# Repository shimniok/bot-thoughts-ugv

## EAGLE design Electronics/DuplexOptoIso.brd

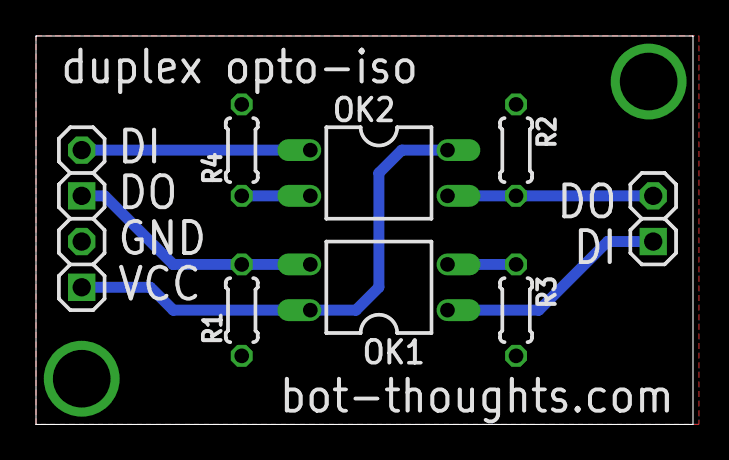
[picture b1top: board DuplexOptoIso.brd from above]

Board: 2 copper layers, 36.5 x 21.6 mm, 9 parts (0 on the bottom side), 8 nets.

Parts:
JP1: 1IN2OUT; 1X02-S
JP2: 1OUT2IN; 1X02-S
JP3: POWER; 1X02-S
OK1, OK2: PC817; DIL04
R1, R2, R3, R4: 0204/5

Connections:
5V: JP3.1, OK1.4, OK2.4
GND: JP3.2, R1.1, R2.1, R3.1, R4.1
IN1: JP1.1, OK1.1
IN2: JP2.2, OK2.1
unnamed: OK1.2, R3.2
unnamed: OK2.2, R4.2
OUT1: JP2.1, OK1.3, R1.2
OUT2: JP1.2, OK2.3, R2.2

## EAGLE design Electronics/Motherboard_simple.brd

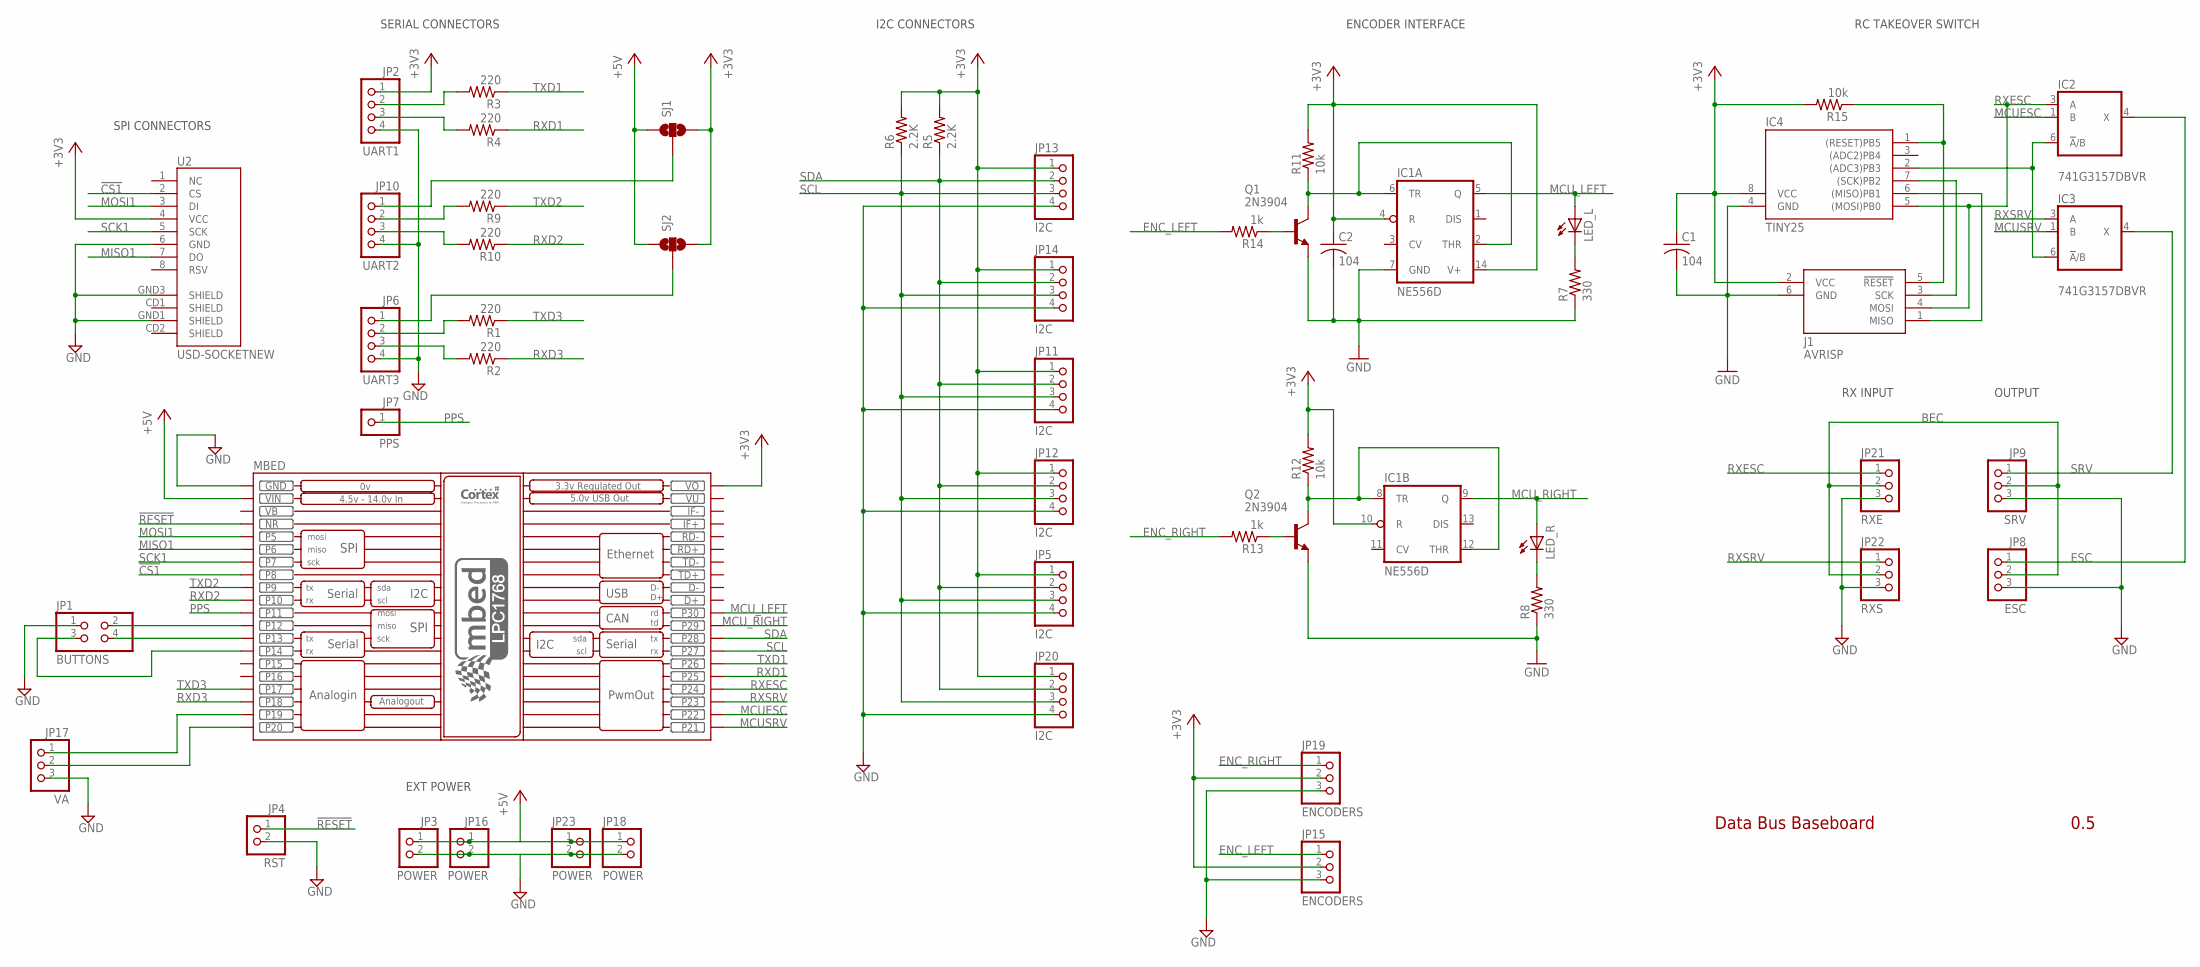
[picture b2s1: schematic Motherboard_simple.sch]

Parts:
C1, C2: 104; C050-025X075
IC1: NE556D; SO14
IC2, IC3: 741G3157DBVR; DBV_R-PDSO-G6
IC4: TINY25; DIL08
J1: AVRISP; CON6P2R
JP1: BUTTONS; 2X02
JP2: UART1; 1X04-S
JP3, JP16, JP18, JP23: POWER; 1X02-S
JP4: RST; 1X02-S
JP5, JP11, JP12, JP13, JP14, JP20: I2C; 1X04-S
JP6: UART3; 1X04-S
JP7: PPS; 1X01-S
JP8: ESC; 1X03-S
JP9: SRV; 1X03-S
JP10: UART2; 1X04-S
JP15, JP19: ENCODERS; 1X03-S
JP17: VA; 1X03-S
JP21: RXE; 1X03-S
JP22: RXS; 1X03-S
LED_L: LED3MM
LED_R: LED3MM
MBED: MBED_NXP_LPC1768; MBED-KIT; MPN 2212S-20SG-85
Q1, Q2: 2N3904; TO92
R1, R2, R3, R4, R9, R10: 220; 0204/5; MPN WCR0805-220RFI
R5, R6: 2.2K; 0204/5
R7, R8: 330; 0204/5
R11, R12, R15: 10k; 0204/5
R13, R14: 1k; 0204/5
SJ1, SJ2: SOLDERJUMPER_2WAYS; SJ_3
U2: USD-SOCKETNEW; MICRO-SD-SOCKET-PP

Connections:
!CS1: MBED.P$8 (P8), U2.2 (CS)
!RESET: JP4.1, MBED.NR
!TRST: IC4.1 ((RESET)PB5), J1.5 (!RESET), R15.1
+3V3: C1.1, C2.1, IC1.4 (R), IC1.10 (R), IC1.14 (V+), IC4.8 (VCC), J1.2 (VCC), JP2.1, JP5.1, JP11.1, JP12.1, JP13.1, JP14.1, JP15.2, JP19.2, JP20.1, MBED.VOUT (VO), R5.2, R6.2, R11.2, R12.2, R15.2, SJ1.3, SJ2.3, U2.4 (VCC)
+5V: JP3.1, JP16.1, JP18.1, JP23.1, MBED.VIN, SJ1.1, SJ2.1
AMP: JP17.2, MBED.P$20 (P20)
BEC: JP8.2, JP9.2, JP21.2, JP22.2
ENC_LEFT: JP15.1, R14.2
ENC_RIGHT: JP19.1, R13.2
ESC: IC2.4 (X), JP8.1
GND: C1.2, C2.2, IC1.7 (GND), IC2.2 (GND), IC3.2 (GND), IC4.4 (GND), J1.6 (GND), JP1.1, JP2.4, JP3.2, JP4.2, JP5.4, JP6.4, JP8.3, JP9.3, JP10.4, JP11.4, JP12.4, JP13.4, JP14.4, JP15.3, JP16.2, JP17.3, JP18.2, JP19.3, JP20.4, JP21.3, JP22.3, JP23.2, MBED.GND, Q1.3 (E), Q2.3 (E), R7.1, R8.1, U2.6 (GND), U2.GND1 (SHIELD), U2.GND3 (SHIELD)
MCUESC: IC2.1 (B), MBED.P$22 (P22)
MCUSRV: IC3.1 (B), MBED.P$21 (P21)
MCU_LEFT: IC1.5 (Q), LED_L.A, MBED.P$30 (P30)
MCU_RIGHT: IC1.9 (Q), LED_R.A, MBED.P$29 (P29)
MISO: IC4.6 ((MISO)PB1), J1.1 (MISO)
MISO1: MBED.P$6 (P6), U2.7 (DO)
MOSI1: MBED.P$5 (P5), U2.3 (DI)
unnamed: JP6.2, R1.2
unnamed: JP6.3, R2.2
unnamed: LED_L.K (C), R7.2
unnamed: LED_R.K (C), R8.2
unnamed: JP1.4, MBED.P$13 (P13)
unnamed: JP17.1, MBED.P$19 (P19)
unnamed: JP1.2, MBED.P$12 (P12)
unnamed: JP1.3, MBED.P$14 (P14)
unnamed: JP2.2, R3.2
unnamed: JP2.3, R4.2
unnamed: IC1.8 (TR), IC1.12 (THR), Q2.1 (C), R12.1
unnamed: IC1.2 (THR), IC1.6 (TR), Q1.1 (C), R11.1
unnamed: Q2.2 (B), R13.1
unnamed: Q1.2 (B), R14.1
unnamed: JP10.2, R9.2
unnamed: JP10.3, R10.2
unnamed: JP10.1, SJ1.2
unnamed: JP6.1, SJ2.2
unnamed: IC2.6 (!A!/B), IC3.6 (!A!/B), IC4.2 ((ADC3)PB3)
PPS: JP7.1, MBED.P$11 (P11)
RXD1: MBED.P$25 (P25), R4.1
RXD2: MBED.P$10 (P10), R10.1
RXD3: MBED.P$18 (P18), R2.1
RXESC: IC2.3 (A), IC4.5 ((MOSI)PB0), J1.4 (MOSI), JP21.1, MBED.P$24 (P24)
RXSRV: IC3.3 (A), JP22.1, MBED.P$23 (P23)
SCK: IC4.7 ((SCK)PB2), J1.3 (SCK)
SCK1: MBED.P$7 (P7), U2.5 (SCK)
SCL: JP5.3, JP11.3, JP12.3, JP13.3, JP14.3, JP20.3, MBED.P$27 (P27), R6.1
SDA: JP5.2, JP11.2, JP12.2, JP13.2, JP14.2, JP20.2, MBED.P$28 (P28), R5.1
SRV: IC3.4 (X), JP9.1
TXD1: MBED.P$26 (P26), R3.1
TXD2: MBED.P$9 (P9), R9.1
TXD3: MBED.P$17 (P17), R1.1
VB: MBED.VB
VCC: IC2.5 (VCC), IC3.5 (VCC)
VU: MBED.VU

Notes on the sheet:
SPI CONNECTORS
I2C CONNECTORS
SERIAL CONNECTORS
Data Bus Baseboard
0.5
EXT POWER
OUTPUT
RX INPUT
RC TAKEOVER SWITCH
ENCODER INTERFACE

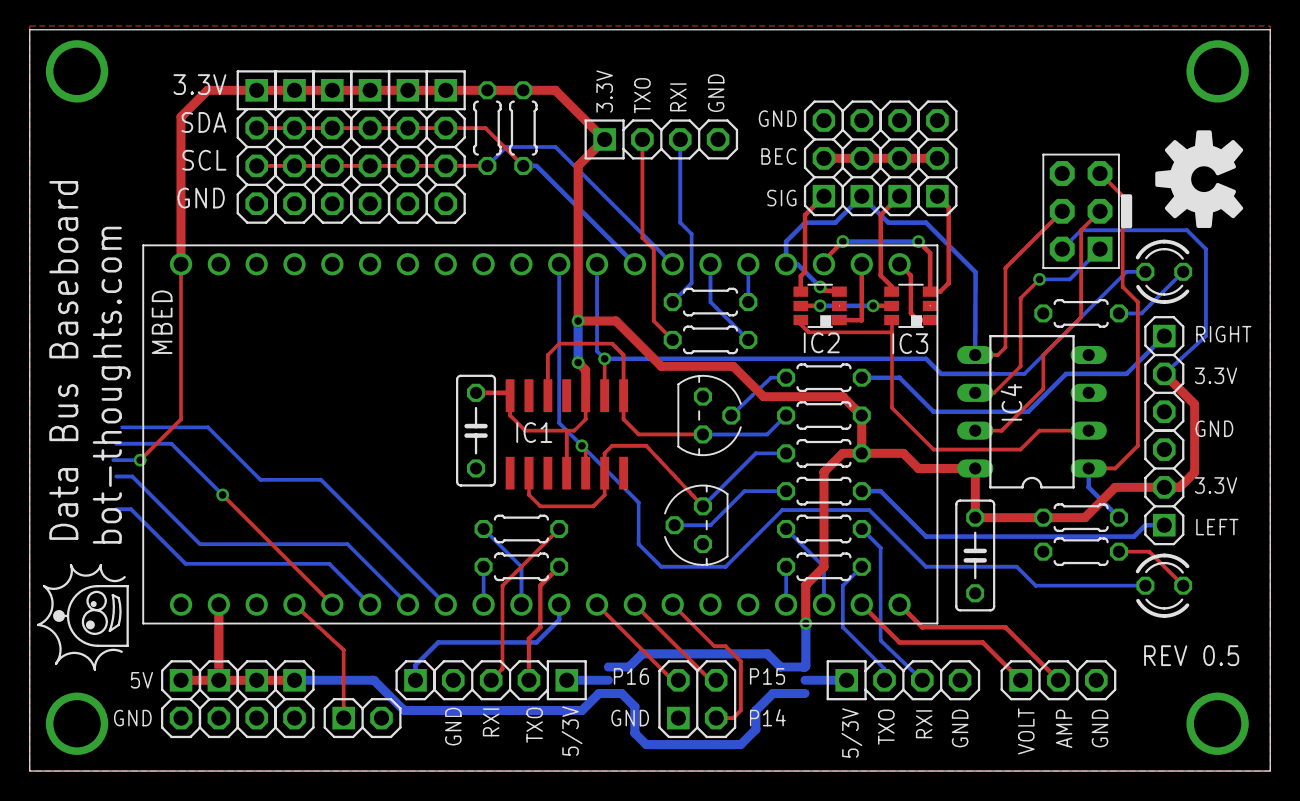
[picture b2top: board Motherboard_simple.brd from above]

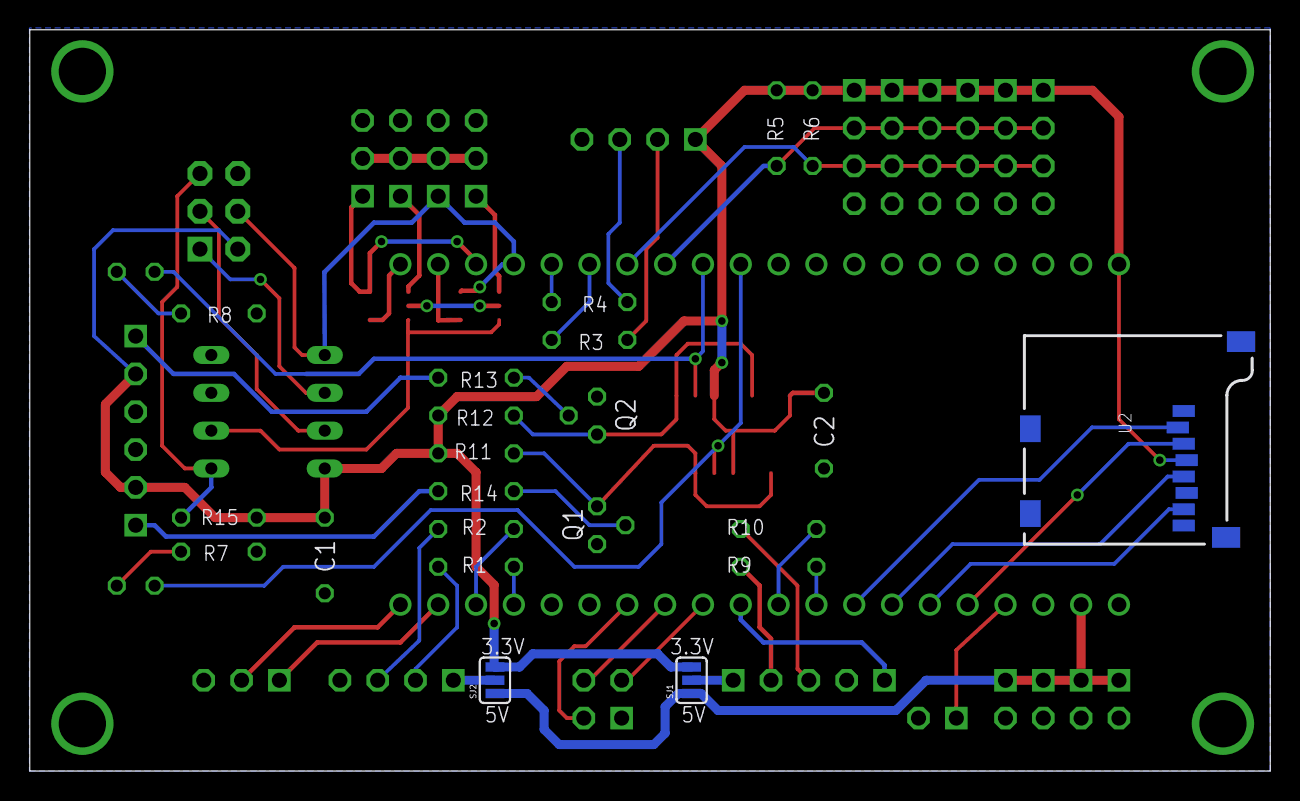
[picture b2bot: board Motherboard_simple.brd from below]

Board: 2 copper layers, 83.3 x 49.8 mm, 53 parts (3 on the bottom side), 52 nets.

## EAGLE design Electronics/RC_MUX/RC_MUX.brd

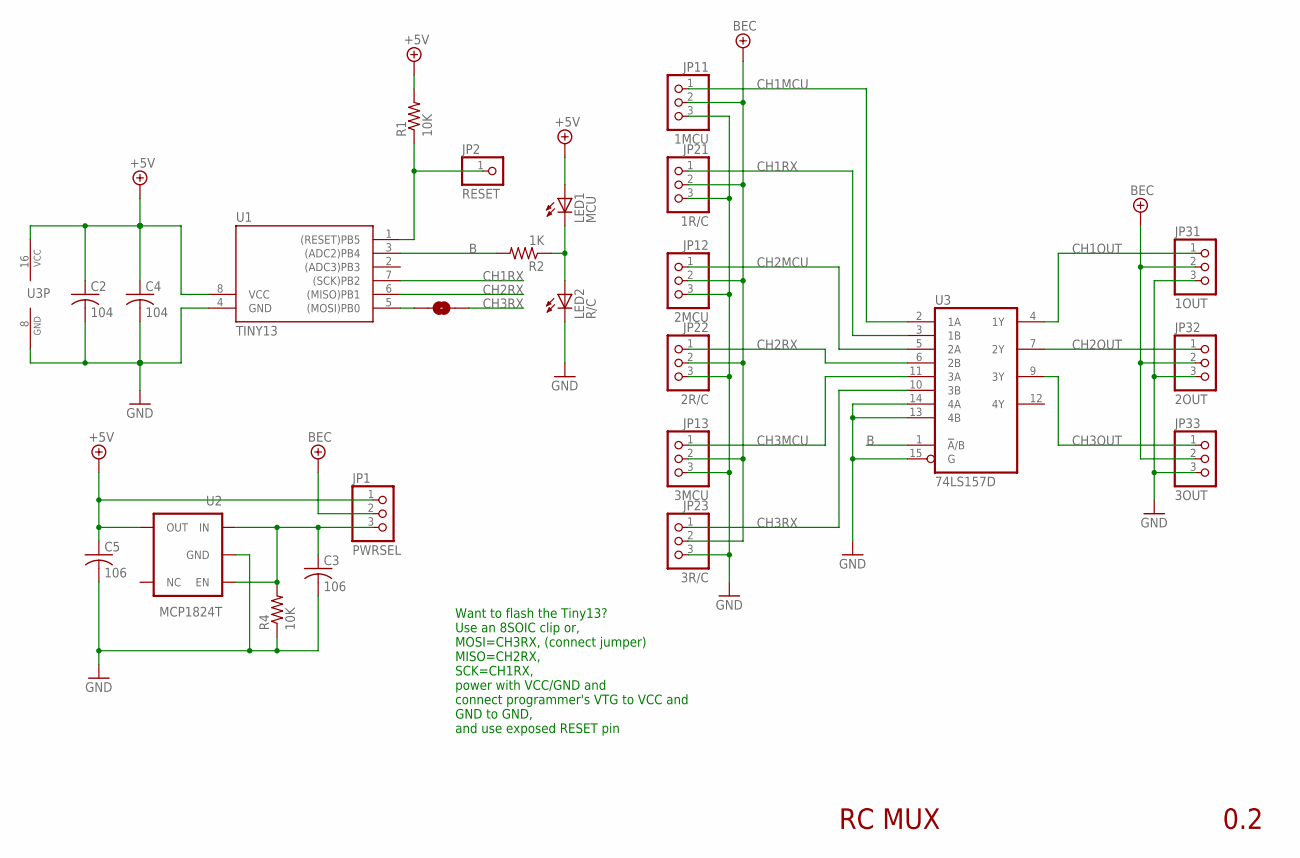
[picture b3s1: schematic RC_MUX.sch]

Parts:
C2, C4: 104; C0603; PARTNO C1608X7R1E104K080AA
C3, C5: 106; C0603; PARTNO CL10A106MP8NNNC
JP1: PWRSEL; 1X03M
JP2: RESET; 1X01-S
JP11: 1MCU; 1X03-S
JP12: 2MCU; 1X03-S
JP13: 3MCU; 1X03-S
JP21: 1R/C; 1X03-S
JP22: 2R/C; 1X03-S
JP23: 3R/C; 1X03-S
JP31: 1OUT; 1X03-S
JP32: 2OUT; 1X03-S
JP33: 3OUT; 1X03-S
LED1: MCU; CHIPLED_1206; PARTNO LH N974-KN-1
LED2: R/C; CHIPLED_1206; PARTNO LG N971-KN-1
R1, R4: 10K; R0603; PARTNO 1622829-1
R2: 1K; R0603; PARTNO RC0603JR-07330RL
SJ1: CH3; SJ_2S-NOTRACE
U1: TINY13; SO08; PARTNO ATTINY13A-SSH
U2: MCP1824T; SOT23-5; PARTNO MCP1824T-5002E/OT
U3: 74LS157D; SO16; PARTNO 74HCT157D,652

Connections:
!RESET: JP2.1, R1.1, U1.1 ((RESET)PB5)
+5V: C2.1, C4.1, C5.1, JP1.1, LED1.A, R1.2, U1.8 (VCC), U2.5 (OUT), U3.16 (VCC)
+7V: JP1.2, JP11.2, JP12.2, JP13.2, JP21.2, JP22.2, JP23.2, JP31.2, JP32.2, JP33.2
B: R2.2, U1.3 ((ADC2)PB4), U3.1 (!A!/B)
CH1MCU: JP11.1, U3.2 (1A)
CH1OUT: JP31.1, U3.4 (1Y)
CH1RX: JP21.1, U1.7 ((SCK)PB2), U3.3 (1B)
CH2MCU: JP12.1, U3.5 (2A)
CH2OUT: JP32.1, U3.7 (2Y)
CH2RX: JP22.1, U1.6 ((MISO)PB1), U3.6 (2B)
CH3MCU: JP13.1, U3.11 (3A)
CH3OUT: JP33.1, U3.9 (3Y)
CH3RX: JP23.1, SJ1.2, U3.10 (3B)
GND: C2.2, C3.2, C4.2, C5.2, JP11.3, JP12.3, JP13.3, JP21.3, JP22.3, JP23.3, JP31.3, JP32.3, JP33.3, LED2.C, R4.1, U1.4 (GND), U2.2 (GND), U3.8 (GND), U3.13 (4B), U3.14 (4A), U3.15 (G)
LEDS: LED1.C, LED2.A, R2.1
unnamed: SJ1.1, U1.5 ((MOSI)PB0)
REGIN: C3.1, JP1.3, R4.2, U2.1 (IN), U2.3 (EN)

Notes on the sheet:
RC MUX
0.2
Want to flash the Tiny13? Use an 8SOIC clip or, MOSI=CH3RX, (connect jumper) MISO=CH2RX, SCK=CH1RX, power with VCC/GND and connect programmer's VTG to VCC and GND to GND, and use exposed RESET pin

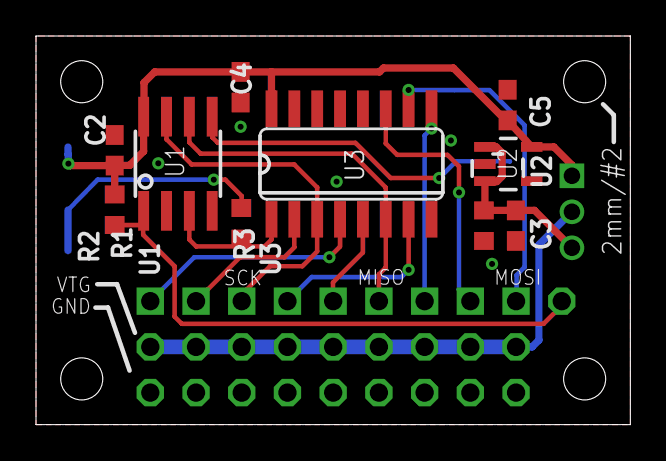
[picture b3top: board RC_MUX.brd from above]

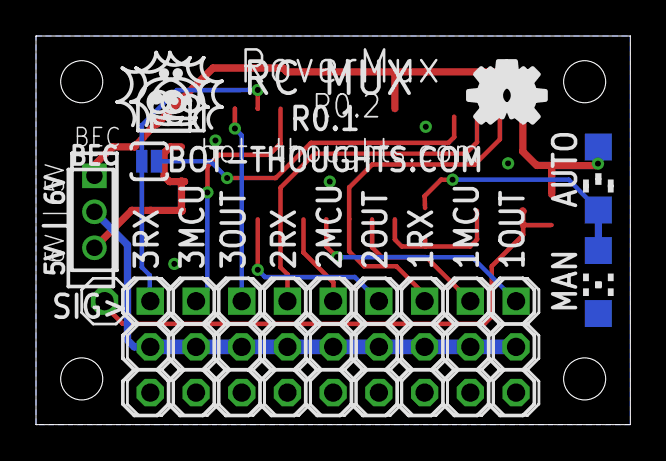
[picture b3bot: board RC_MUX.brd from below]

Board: 2 copper layers, 33.0 x 21.6 mm, 24 parts (14 on the bottom side), 17 nets.

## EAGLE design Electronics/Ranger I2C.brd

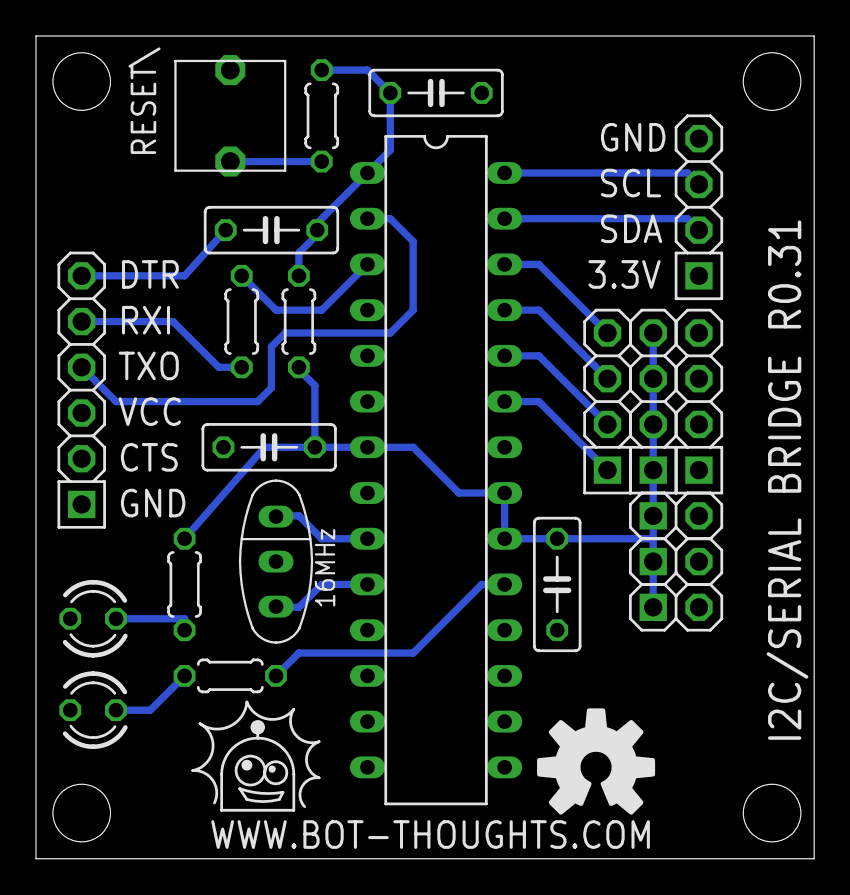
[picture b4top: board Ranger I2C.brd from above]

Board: 2 copper layers, 43.2 x 45.7 mm, 22 parts (0 on the bottom side), 19 nets.

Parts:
C1, C2, C3, C4: 0.1uF; C050-025X075
IC1: ATmega328P; DIL28-3
J1, J7, J8: PWR; 1X02-S
J2: I2C; 1X04-S
J3: FTDI; 1X06-S
J4: AN; 1X04-S
J5: 5V; 1X04-S
J6: GND; 1X04-S
LED1, LED2: STAT1; LED3MM
Q1: 16MHz; CSTLS_G9
R1, R6: 1K; 0204/5
R2, R5, R7: 330; 0204/5
S1: RESET\; EVQ11X09

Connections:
5V: C3.1, C4.1, IC1.7, IC1.20, IC1.21, J1.1, J5.1, J5.2, J5.3, J5.4, J7.1, J8.1, R1.2, R7.1
<RXD/TXO: IC1.2, J3.4
ADC0: IC1.23, J4.1
ADC1: IC1.24, J4.2
ADC2: IC1.25, J4.3
ADC3: IC1.26, J4.4
DTR: C1.2, J3.6
GND: C2.2, C3.2, C4.2, IC1.8, IC1.22, J1.2, J2.4, J3.1, J6.1, J6.2, J6.3, J6.4, J7.2, J8.2, LED1.K, LED2.K, Q1.2, S1.1
LV_TXD/RXI>: J3.5, R6.2
unnamed: IC1.9, Q1.1
unnamed: IC1.10, Q1.3
unnamed: LED1.A, R2.2
unnamed: IC1.19, R2.1
unnamed: C1.1, C2.1, IC1.1, R1.1, R5.1
unnamed: R5.2, S1.2
unnamed: LED2.A, R7.2
RXI/TXD>: IC1.3, R6.1
SCL: IC1.28, J2.3
SDA: IC1.27, J2.2

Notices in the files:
parts and their libraries:
SparkFun: Licensing: CC v3.0 Share-Alike You are welcome to use this library for commercial purposes.
